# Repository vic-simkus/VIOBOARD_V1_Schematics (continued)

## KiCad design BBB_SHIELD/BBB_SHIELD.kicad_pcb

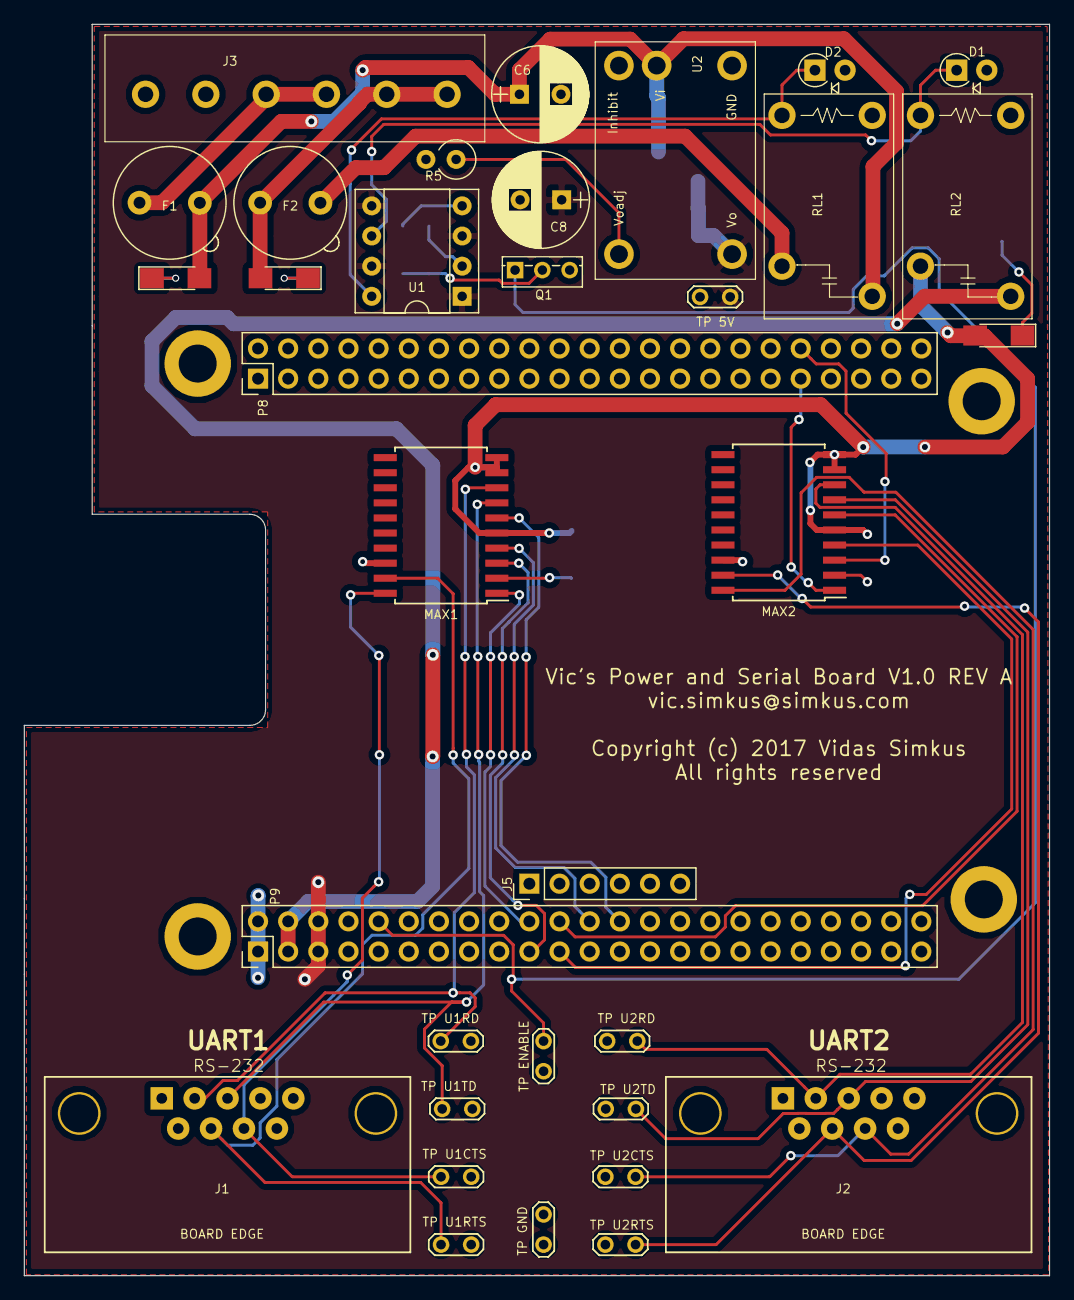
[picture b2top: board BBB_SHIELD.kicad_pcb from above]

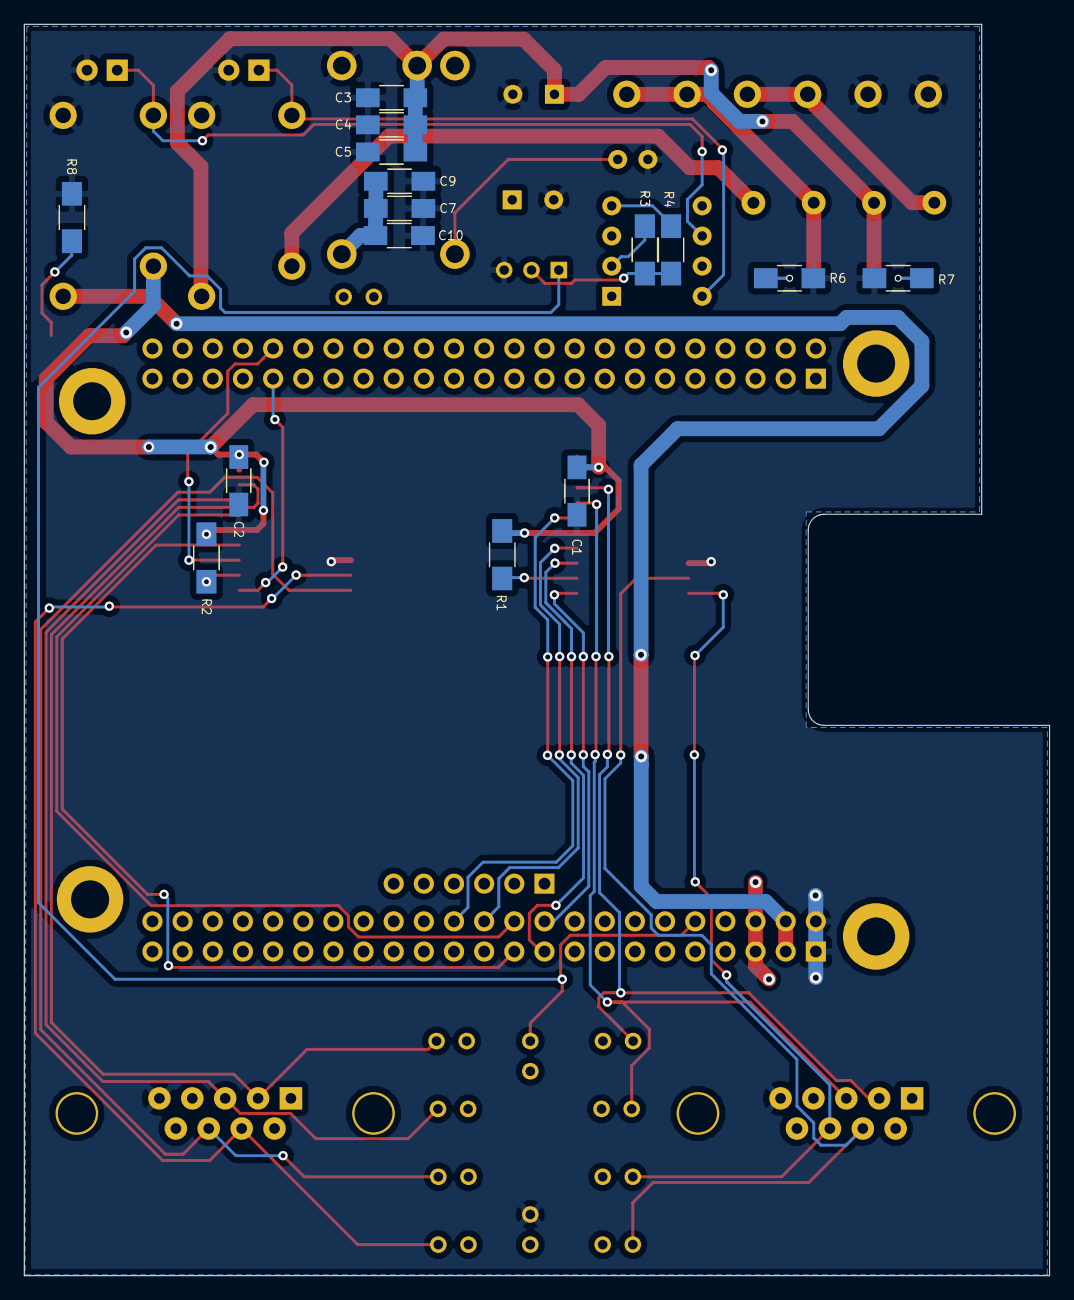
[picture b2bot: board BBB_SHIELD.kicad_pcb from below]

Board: 2 copper layers, 86.4 x 105.4 mm, 49 parts (15 on the bottom side), 36 nets.

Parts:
C1, C2: .1uF; C_1206_HandSoldering
C3, C10: 2.2uF; C_1206_HandSoldering
C4, C9: 1uF; C_1206_HandSoldering
C5, C7: 10uF; C_1206_HandSoldering
C6, C8: 180uF; CP_Radial_D8.0mm_P3.50mm
D1, D2: D; D_A-405_P2.54mm_Vertical_AnodeUp
F1, F2: Fuse; Fuseholder_Fuse_TR5_Littlefuse-No560_No460
J1: UART1; D_SUB_9_RIGHT
J2: UART2; D_SUB_9_RIGHT
J3: PWR_CONN; OSTTA064163
J4: TEST_1P; Test_Point_2Pads
J5: Screw_Terminal_1x06; Pin_Header_Straight_1x06_Pitch2.54mm
J6: TP_U1_CTS; Test_Point_2Pads
J7: TP_U1_RD; Test_Point_2Pads
J8: TP_U2_CTS; Test_Point_2Pads
J9: TP_U2_RD; Test_Point_2Pads
J10: TP_EN; Test_Point_2Pads
J11: TP_U1_TD; Test_Point_2Pads
J12: TP_U1_RTS; Test_Point_2Pads
J13: TP_U2_TD; Test_Point_2Pads
J14: TP_U2_RTS; Test_Point_2Pads
J15: TP_GND; Test_Point_2Pads
LED1: 24V_SW; LED_1206_HandSoldering
LED2: 24V_PROT; LED_1206_HandSoldering
LED3: 33V_SW; LED_1206_HandSoldering
MAX1, MAX2: MAX3233E; SOIC-20W_7.5x12.8mm_Pitch1.27mm
P8: P8; Pin_Header_Straight_2x23_Pitch2.54mm
P9: P9; Pin_Header_Straight_2x23_Pitch2.54mm
Q1: F3055L; TO-251_IPAK_Vertical
R1, R2: 10K; R_1206_HandSoldering
R3, R4, R8: 470; R_1206_HandSoldering
R5: 21K; R_Axial_DIN0309_L9.0mm_D3.2mm_P2.54mm_Vertical
R6, R7: 4.7K; R_1206_HandSoldering
RL1: 24V RELAY; OJ-SH-105LMH000-ND
RL2: 3.3V RELAY; OJ-SH-105LMH000-ND
U1: TLP222A-2-C; DIP-8_W7.62mm_Socket
U2: PTN78000WAH; PTN78000H

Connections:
/POWER_CONTROL/ENABLE: J10.1, P9.10, Q1.1
/POWER_CONTROL/VDD_24V_IN: F1.1, J3.3, J3.4
/POWER_CONTROL/VDD_24V_SW_OUT: F2.1, J3.5, J3.6, LED1.2
/SERIAL_IO/DB9_U1_CTS: J1.8, J6.1, MAX1.20
/SERIAL_IO/DB9_U1_RD(RX): J1.2, J7.1, MAX1.8
/SERIAL_IO/DB9_U1_RTS: J1.7, J12.1, MAX1.19
/SERIAL_IO/DB9_U1_TD(TX): J1.3, J11.1, MAX1.7
/SERIAL_IO/DB9_U2_CTS: J2.8, J8.1, MAX2.20
/SERIAL_IO/DB9_U2_RD(RX): J2.2, J9.1, MAX2.8
/SERIAL_IO/DB9_U2_RTS: J2.7, J14.1, MAX2.19
/SERIAL_IO/DB9_U2_TD(TX): J2.3, J13.1, MAX2.7
/U1_CTS: MAX1.1, P9.20
/U1_RTS: MAX1.3, P9.19
/U1_RX: MAX1.6, P9.26
/U1_TX: MAX1.4, P9.24
/U2_CTS: MAX2.1, P8.37
/U2_RTS: MAX2.3, P8.38
/U2_RX: MAX2.6, P9.22
/U2_TX: MAX2.4, P9.21
GND: C1.2, C2.2, C3.2, C4.2, C5.2, C6.2, C7.2, C8.2, C9.2, C10.2, D1.2, D2.2, J1.5, J2.5, J3.1, J3.2, J15.1, MAX1.18, MAX2.18, P9.1, P9.2, Q1.3, R5.2, R6.2, R7.2, R8.2, RL1.2, RL2.2, U2.1
unnamed: D1.1, RL2.1, U1.6
unnamed: D2.1, RL1.1, U1.8
unnamed: LED1.1, R6.1
unnamed: LED2.1, R7.1
unnamed: LED3.1, R8.1
unnamed: MAX1.2, R1.2
unnamed: MAX2.2, R2.2
unnamed: Q1.2, R3.2, R4.2
unnamed: R3.1, U1.2
unnamed: R4.1, U1.4
unnamed: R5.1, U2.4
VDD_5V_PROT: C7.1, C8.1, C9.1, C10.1, J4.1, P9.5, P9.6, U1.1, U1.3, U1.5, U1.7, U2.5
VDD_24V_PROT: C3.1, C4.1, C5.1, C6.1, F1.2, LED2.2, RL1.4, U2.2
VDD_24V_SW: F2.2, RL1.3
VDD_33V: P9.3, P9.4, RL2.4
VDD_33V_SW: C1.1, C2.1, LED3.2, MAX1.5, MAX1.9, MAX1.10, MAX2.5, MAX2.9, MAX2.10, R1.1, R2.1, RL2.3

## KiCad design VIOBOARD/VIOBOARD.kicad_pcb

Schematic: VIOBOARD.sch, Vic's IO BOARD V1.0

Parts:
J1: Screw_Terminal_1x04; OSTTA044163; MFGPN OSTTA044163
J2: Conn_02x02_Top_Bottom; Pin_Header_Straight_2x02_Pitch1.27mm
J8, J9: TEST_1P; Test_Point_2Pads
SW1: BOARD_RESET; SW_PUSH_6mm; MFGPN 1825910-6

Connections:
/IOCONTROLLER/IO_RESET: J2.1; also elsewhere on the board
/comm_controller/COMM_RESET: J2.3; also elsewhere on the board
/power_protection/VDD_24V: J1.1, J1.2; also elsewhere on the board
unnamed: J2.2, J2.4
RESET: SW1.2
VDD_24V_PROT: J9.1; also elsewhere on the board

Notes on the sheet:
INCOMMING POWER

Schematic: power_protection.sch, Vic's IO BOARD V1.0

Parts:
C1: 0.012uF 50V; C_1206; MFGPN 12065C123KAT2A
C2: 0.1uF 50V; C_1206; MFGPN GCM319R71H104KA37D
C3: 1uF 50V; C_1206
C4: 10uF 50V; C_1206
C5: 1nF 50V; C_1206; MFGPN GRM319R71H102KA01D
D1: 24V_TRIAC; TO-220_Vertical; MFGPN ACTT6X-800E,127
D2: D_ALT; DO-214AA; MFGPN SMBJ26A
F1: 24V_IN; Fuseholder_Fuse_TR5_Littlefuse-No560_No460; MFGPN 56000001319
LED11: Vf=2V; LED_0805; MFGPN LS R976-NR-1
R2: 23.2K 1%; R_0805; MFGPN CRCW080523K2FKEA
R3: 2.49K 1%; R_0805; MFGPN RC0805FR-072K49L
R4: 910 1%; R_0805; MFGPN CRCW0805910RFKEA
R5: 4.7K 1%; R_0805; MFGPN CRCW08054K70FKEA
R65: 100 1%; R_2512; MFGPN CRM2512-FX-1000ELF
TL1: 24V_REF; TO-92_Inline_Wide; MFGPN TL431BCLPR

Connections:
/power_protection/VDD_24V: R65.2; also elsewhere on the board
/power_protection/VDD_24V_SHUNT: D1.3, R4.2, TL1.1
unnamed: C1.1, C2.1, C3.1, C4.1, F1.1, R65.1
unnamed: C5.1, R2.2, R3.1, TL1.3
unnamed: LED11.1, R5.1
VDD_24V_PROT: D1.1, D2.1, F1.2, LED11.2, R2.1, R4.1; also elsewhere on the board

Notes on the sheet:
Vgt = 1V
Vref=2.507V
Vout = 2.520 @ Vin = 26 I = 1mA @ 26V
24V PROT
TL431
ACTT6X-800E

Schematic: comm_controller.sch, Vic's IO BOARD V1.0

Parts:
C6: 18pF 50V; C_0805; MFGPN CL21C180JBANNNC
C7: 20pF 50V; C_0805; MFGPN C0805C200K5GACTU
C8: 10uF 50V; C_1206
J3: BOARD_COMM; D_SUB_9_RIGHT; MFGPN 3-1634580-2
J12: TP SCL; Test_Point_2Pads
J13: TP SDA; Test_Point_2Pads
J14: TP_CTS; Test_Point_2Pads
J15: TP_TD; Test_Point_2Pads
J16: TP_RTS; Test_Point_2Pads
J17: TP_RD; Test_Point_2Pads
J18: TP_GND; Test_Point_2Pads
J19: CONN_01X06; Pin_Header_Angled_1x06_Pitch2.54mm; MFGPN 0022052061
LED14: Vf=2V; LED_0805; MFGPN LY R976-PS-36
PIC1: PIC24FVXXKA302; PIC_SOIC-28; MFGPN PIC24FV32KA302-I/SO
R6, R7: 4.7K 1%; R_0805; MFGPN CRCW08054K70FKEA
R8: 10K 1%; R_0805; MFGPN CRCW080510K0FKTA
R9: 470 1%; R_0805; MFGPN CRCW0805470RFKEA
Y1: 8MHz; Crystal_HC49-4H_Vertical; MFGPN 9B-8.000MEEJ-B

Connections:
/I2C_SCL: J12.1, PIC1.15, R6.2; also elsewhere on the board
/I2C_SDA: J13.1, PIC1.14, R7.2; also elsewhere on the board
/comm_controller/COMM_RESET: J19.1, PIC1.1, R8.1; also elsewhere on the board
/comm_controller/CTS: J3.8, J14.1; also elsewhere on the board
/comm_controller/RD(RX): J3.2, J17.1; also elsewhere on the board
/comm_controller/RTS: J3.7, J16.1; also elsewhere on the board
/comm_controller/TD(TX): J3.3, J15.1; also elsewhere on the board
/comm_controller/U1CTS: PIC1.17; also elsewhere on the board
/comm_controller/U1RTS: PIC1.18; also elsewhere on the board
/comm_controller/U1RX: PIC1.6; also elsewhere on the board
/comm_controller/U1TX: PIC1.16; also elsewhere on the board
unnamed: C6.1, PIC1.9, Y1.1
unnamed: C7.1, PIC1.10, Y1.2
unnamed: C8.2, PIC1.20
unnamed: J19.4, PIC1.4
unnamed: J19.5, PIC1.5
unnamed: LED14.1, R9.2
unnamed: LED14.2, PIC1.25
VDD_5V_PROT: J19.2, PIC1.13, PIC1.28, R6.1, R7.1, R8.2; also elsewhere on the board

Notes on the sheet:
RB0 - ICSP - PGED
RB1 - ICSP - PGEC
RB2 - U1RX - RS1_OUT
RB5 - ASDA
RB6 - ASCL
RB7 - U1TX - TTL1_IN
RB8 - U1CTS - RS2_OUT
RB9 - U1RTS - TTL2_IN
RB14 - GPIO
SDA
SCL
BOM - 2017-06-09
COMMHTBT

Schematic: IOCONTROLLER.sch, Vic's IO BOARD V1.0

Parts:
C18: 20pF 50V; C_0805; MFGPN C0805C200K5GACTU
C19: 18pF 50V; C_0805; MFGPN CL21C180JBANNNC
J20: CONN_01X06; Pin_Header_Angled_1x06_Pitch2.54mm; MFGPN 0022052061
R10: 10K 1%; R_0805; MFGPN CRCW080510K0FKTA
Y2: 10MHz; Crystal_HC49-4H_Vertical; MFGPN 9B-10.000MEEJ-B
dsPIC1: dsPIC30F4013; TQFP-44_10x10mm_Pitch0.8mm; MFGPN DSPIC30F4013-30I/PT

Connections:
/I2C_SCL: dsPIC1.44; also elsewhere on the board
/I2C_SDA: dsPIC1.1; also elsewhere on the board
/IOCONTROLLER/AI_ENABLE/RC13: dsPIC1.32; also elsewhere on the board
/IOCONTROLLER/AI_FAULT/R0: dsPIC1.9; also elsewhere on the board
/IOCONTROLLER/AI_PROT/PP_AI_FAULT_LED: dsPIC1.36; also elsewhere on the board
/IOCONTROLLER/AN3/RB3/420_4: dsPIC1.22; also elsewhere on the board
/IOCONTROLLER/AN4/RB4/420_3: dsPIC1.23; also elsewhere on the board
/IOCONTROLLER/AN5/RB5/420_2: dsPIC1.24; also elsewhere on the board
/IOCONTROLLER/AN8/RB8/420_1: dsPIC1.27; also elsewhere on the board
/IOCONTROLLER/AUX_LED: dsPIC1.35; also elsewhere on the board
/IOCONTROLLER/BUS_IN_LED: dsPIC1.37; also elsewhere on the board
/IOCONTROLLER/BUS_OUT_LED: dsPIC1.41; also elsewhere on the board
/IOCONTROLLER/DIGITAL_OUT/PP_DO_FAULT_LED: dsPIC1.38; also elsewhere on the board
/IOCONTROLLER/DO1/RF1: dsPIC1.4; also elsewhere on the board
/IOCONTROLLER/DO2/RF0: dsPIC1.5; also elsewhere on the board
/IOCONTROLLER/DO3/RF6: dsPIC1.43; also elsewhere on the board
/IOCONTROLLER/DO4/RF4: dsPIC1.3; also elsewhere on the board
/IOCONTROLLER/DO_ENABLE/RF5: dsPIC1.2; also elsewhere on the board
/IOCONTROLLER/DO_FAULT/RD1: dsPIC1.8; also elsewhere on the board
/IOCONTROLLER/DSPIC_PGC: J20.5, dsPIC1.25
/IOCONTROLLER/DSPIC_PGD: J20.4, dsPIC1.26
/IOCONTROLLER/HTBT_LED: dsPIC1.42; also elsewhere on the board
/IOCONTROLLER/IO_RESET: J20.1, R10.1, dsPIC1.18; also elsewhere on the board
/IOCONTROLLER/RB1/AN1/ICD3: dsPIC1.20; also elsewhere on the board
/IOCONTROLLER/RB2/AN2/ICD4: dsPIC1.21; also elsewhere on the board
/IOCONTROLLER/RB9/AN9/ICD1: dsPIC1.15; also elsewhere on the board
/IOCONTROLLER/RB10/AN10/ICD2: dsPIC1.14; also elsewhere on the board
/IOCONTROLLER/VREF+/VREF+: dsPIC1.19; also elsewhere on the board
unnamed: C18.2, Y2.1, dsPIC1.31
unnamed: C19.2, Y2.2, dsPIC1.30
VDD_5V_PROT: J20.2, R10.2, dsPIC1.7, dsPIC1.17, dsPIC1.28, dsPIC1.40; also elsewhere on the board

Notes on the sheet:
BOM - 2017-06-09

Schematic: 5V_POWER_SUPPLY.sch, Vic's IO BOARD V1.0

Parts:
C44: 2.2uF 50V; C_1206; MFGPN GCM31CR71H225KA55L
C45: 1uF 50V; C_1206; MFGPN GRM31CR71H105KA61L
C46, C48: 10uF 50V; C_1206; MFGPN CL31B106KBHNNNE
C47, C49: 180uF; CP_Radial_D8.0mm_P3.50mm; MFGPN EEU-FC1H181L
C50: 1uF 50V; C_0805; MFGPN CL21B105KBFNNNF
C51: 2.2uF 50V; C_0805; MFGPN C2012X7R1H225K125AC
J11: TEST_1P; Test_Point_2Pads
R45: 21K 1%; R_0805; MFGPN CRCW080521K0FKEA
R66, R67, R68, R69: 0 1%; R_0805; MFGPN CRCW08050000Z0EBC
U9: PTN78000WAH; PTN78000H; MFGPN PTN78000WAH

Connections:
unnamed: C44.1, R66.2
unnamed: C45.1, R67.2
unnamed: C46.1, R68.2
unnamed: C47.1, R69.2
unnamed: R45.1, U9.4
VDD_5V_PROT: C48.1, C49.1, C50.1, C51.1, J11.1, U9.5; also elsewhere on the board
VDD_24V_PROT: R66.1, R67.1, R68.1, R69.1, U9.2; also elsewhere on the board

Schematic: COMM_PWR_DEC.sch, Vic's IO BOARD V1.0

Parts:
C10: 0.01uF 50V; C_0805; MFGPN CL21B103KBANNNC
C11: 0.1uF 50V; C_0805; MFGPN CL21B104KBCNNNC
C12: 1uF 50V; C_0805; MFGPN CL21B105KBFNNNF
C13: 10uF 50V; C_1206

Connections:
VDD_5V_PROT: C10.1, C11.1, C12.1, C13.1; also elsewhere on the board

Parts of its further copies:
C14: 0.01uF 50V; C_0805; MFGPN CL21B103KBANNNC
C15: 0.1uF 50V; C_0805; MFGPN CL21B104KBCNNNC
C16: 1uF 50V; C_0805; MFGPN CL21B105KBFNNNF
C17: 10uF 50V; C_1206

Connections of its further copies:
VDD_5V_PROT: C14.1, C15.1, C16.1, C17.1; also elsewhere on the board

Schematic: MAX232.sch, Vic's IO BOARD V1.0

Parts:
C60, C61, C62, C63, C64: 1uF 50V; C_0805; MFGPN CL21B105KBFNNNF
U1: MAX232I; SOIC-16_3.9x9.9mm_Pitch1.27mm; MFGPN MAX232ID

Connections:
/comm_controller/CTS: U1.8 (R2IN); also elsewhere on the board
/comm_controller/RD(RX): U1.13 (R1IN); also elsewhere on the board
/comm_controller/RTS: U1.7 (T2OUT); also elsewhere on the board
/comm_controller/TD(TX): U1.14 (T1OUT); also elsewhere on the board
/comm_controller/U1CTS: U1.9 (R2OUT); also elsewhere on the board
/comm_controller/U1RTS: U1.10 (T2IN); also elsewhere on the board
/comm_controller/U1RX: U1.12 (R1OUT); also elsewhere on the board
/comm_controller/U1TX: U1.11 (T1IN); also elsewhere on the board
unnamed: C60.1, U1.1 (C1+)
unnamed: C60.2, U1.3 (C1-)
unnamed: C61.1, U1.4 (C2+)
unnamed: C61.2, U1.5 (C2-)
unnamed: C62.1, U1.2 (VS+)
unnamed: C63.1, U1.6 (VS-)
VDD_5V_PROT: C64.1, U1.16 (VCC); also elsewhere on the board

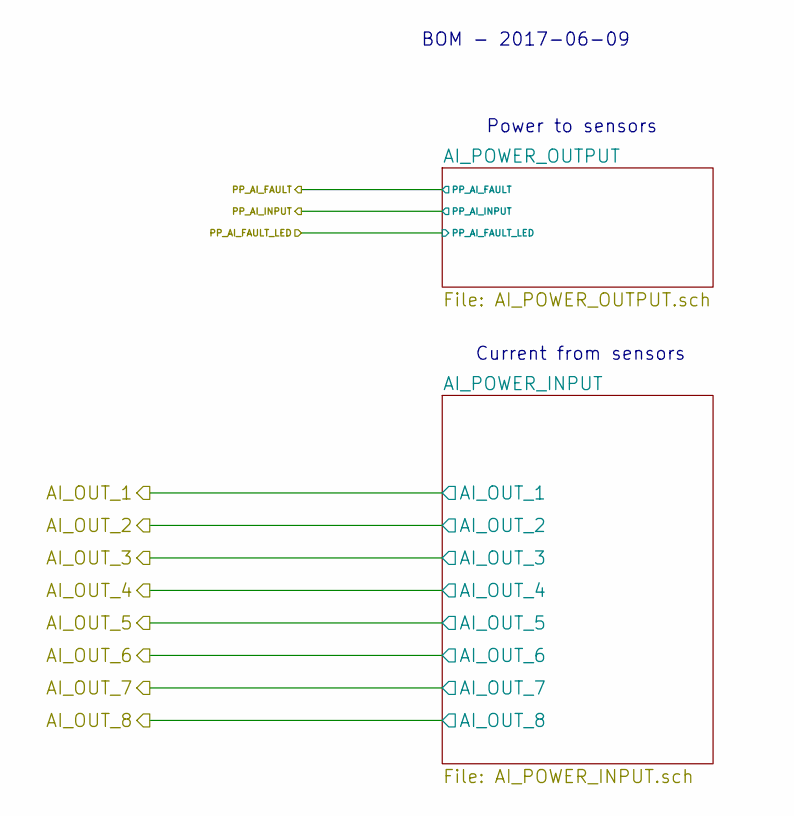
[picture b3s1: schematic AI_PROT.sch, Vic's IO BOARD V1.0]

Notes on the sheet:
Power to sensors
Current from sensors
BOM - 2017-06-09

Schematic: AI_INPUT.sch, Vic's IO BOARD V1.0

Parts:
C21: 0.01uF 50V; C_0805; MFGPN CL21B103KBANNNC
C22: 0.1uF 50V; C_0805; MFGPN CL21B104KBCNNNC
C23, C52, C53, C54, C55, C56, C57, C58, C59: 1uF 50V; C_0805; MFGPN CL21B105KBFNNNF
C24: 10uF 50V; C_1206
R20, R22, R24, R28: 910 1%; R_0805; MFGPN RC2012F822CS
R21, R23, R26, R30: 8.2K 1%; R_0805; MFGPN CRCW0805910RFKEA
R25, R27, R29, R31: 250 0.1%; R_Axial_DIN0309_L9.0mm_D3.2mm_P2.54mm_Vertical; MFGPN CMF55250R00BHEK
R32, R33, R34, R35: 1K 0.1%; R_0805; MFGPN ERJ-PB6B1001V
R78, R79, R80, R81, R82, R83, R84, R85: 1K 1%; R_0805; MFGPN CRCW08051K00FKEA
U5: MCP6004_C; SOIC-14_3.9x8.7mm_Pitch1.27mm; MFGPN MCP6004T-I/SL

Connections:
/IOCONTROLLER/AI_INPUT/AI_IN_420_1: R31.2, R80.1; also elsewhere on the board
/IOCONTROLLER/AI_INPUT/AI_IN_420_2: R29.2, R82.1; also elsewhere on the board
/IOCONTROLLER/AI_INPUT/AI_IN_420_3: R27.2, R84.1; also elsewhere on the board
/IOCONTROLLER/AI_INPUT/AI_IN_420_4: R25.2, R85.1; also elsewhere on the board
/IOCONTROLLER/AI_INPUT/AI_IN_ICD_1: R35.2, U5.3; also elsewhere on the board
/IOCONTROLLER/AI_INPUT/AI_IN_ICD_2: R34.2, U5.5; also elsewhere on the board
/IOCONTROLLER/AI_INPUT/AI_IN_ICD_3: R33.2, U5.10; also elsewhere on the board
/IOCONTROLLER/AI_INPUT/AI_IN_ICD_4: R32.2, U5.12; also elsewhere on the board
/IOCONTROLLER/AI_INPUT/Vina-: R28.2, R30.2, U5.2
/IOCONTROLLER/AI_INPUT/Vinb-: R24.2, R26.2, U5.6
/IOCONTROLLER/AI_INPUT/Vinc-: R22.2, R23.2, U5.9
/IOCONTROLLER/AI_INPUT/Vind-: R20.2, R21.2, U5.13
/IOCONTROLLER/AI_INPUT/Vouta: R30.1, R83.1, U5.1
/IOCONTROLLER/AI_INPUT/Voutb: R26.1, R81.1, U5.7
/IOCONTROLLER/AI_INPUT/Voutc: R23.1, R79.1, U5.8
/IOCONTROLLER/AI_INPUT/Voutd: R21.1, R78.1, U5.14
/IOCONTROLLER/AN3/RB3/420_4: C58.2, R85.2; also elsewhere on the board
/IOCONTROLLER/AN4/RB4/420_3: C56.2, R84.2; also elsewhere on the board
/IOCONTROLLER/AN5/RB5/420_2: C54.2, R82.2; also elsewhere on the board
/IOCONTROLLER/AN8/RB8/420_1: C52.2, R80.2; also elsewhere on the board
/IOCONTROLLER/RB1/AN1/ICD3: C55.1, R79.2; also elsewhere on the board
/IOCONTROLLER/RB2/AN2/ICD4: C53.1, R78.2; also elsewhere on the board
/IOCONTROLLER/RB9/AN9/ICD1: C59.1, R83.2; also elsewhere on the board
/IOCONTROLLER/RB10/AN10/ICD2: C57.1, R81.2; also elsewhere on the board
VDD_5V_PROT: C21.2, C22.1, C23.1, C24.1, U5.4; also elsewhere on the board

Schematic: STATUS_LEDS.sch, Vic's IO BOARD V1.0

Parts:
LED2: Vf=2V; LED_0805; MFGPN LY R976-PS-36
LED3, LED4, LED5: Vf=2V; LED_0805; MFGPN LS R976-NR-1
R1, R46, R47, R48: 470 1%; R_0805; MFGPN CRCW0805470RFKEA

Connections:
/IOCONTROLLER/AUX_LED: LED5.2; also elsewhere on the board
/IOCONTROLLER/BUS_IN_LED: LED3.2; also elsewhere on the board
/IOCONTROLLER/BUS_OUT_LED: LED4.2; also elsewhere on the board
/IOCONTROLLER/HTBT_LED: LED2.2; also elsewhere on the board
unnamed: LED2.1, R1.2
unnamed: LED3.1, R46.2
unnamed: LED4.1, R47.2
unnamed: LED5.1, R48.2

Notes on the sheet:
BOM - 2017-06-09
HTBT LED is yellow

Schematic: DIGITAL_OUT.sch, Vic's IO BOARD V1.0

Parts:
D20, D21, D22, D23: D_ALT; D_SOD-323_CUSTOM; MFGPN CUS08F30,H3F
J7: Screw_Terminal_1x04; OSTTA044163; MFGPN OSTTA044163
LED6, LED7, LED8, LED9: Vf=2V; LED_0805; MFGPN LS R976-NR-1
R49, R50, R51, R52: 470 1%; R_0805; MFGPN CRCW0805470RFKEA
R61, R62, R63, R64: 100 1%; R_0805; MFGPN ERJ-P06F1000V
R86, R87, R88, R89: 4.7K 1%; R_0805; MFGPN CRCW08054K70FKEA
TLPA1: TLP222A-2-C; DIP-8_W7.62mm_Socket; MFGPN TLP222A-2(F)
TLPB1: TLP222A-2-C; DIP-8_W7.62mm_Socket; MFGPN TLP222A-2(F)

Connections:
/IOCONTROLLER/DIGITAL_OUT/DO_POWER_OUT: TLPA1.5, TLPA1.7, TLPB1.5, TLPB1.7; also elsewhere on the board
/IOCONTROLLER/DO1/RF1: TLPA1.3; also elsewhere on the board
/IOCONTROLLER/DO2/RF0: TLPA1.1; also elsewhere on the board
/IOCONTROLLER/DO3/RF6: TLPB1.1; also elsewhere on the board
/IOCONTROLLER/DO4/RF4: TLPB1.3; also elsewhere on the board
unnamed: D20.1, R61.2
unnamed: D20.2, LED6.2, TLPA1.6
unnamed: D21.1, R62.2
unnamed: D21.2, LED7.2, TLPA1.8
unnamed: D22.1, R63.2
unnamed: D22.2, LED8.2, TLPB1.6
unnamed: D23.1, R64.2
unnamed: D23.2, LED9.2, TLPB1.8
unnamed: J7.1, R61.1
unnamed: J7.2, R62.1
unnamed: J7.3, R63.1
unnamed: J7.4, R64.1
unnamed: LED6.1, R86.1
unnamed: LED7.1, R87.1
unnamed: LED8.1, R88.1
unnamed: LED9.1, R89.1
unnamed: R49.1, TLPB1.2
unnamed: R50.1, TLPB1.4
unnamed: R51.1, TLPA1.2
unnamed: R52.1, TLPA1.4

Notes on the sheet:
DOUT
DOUT2
DOUT3
DOUT4

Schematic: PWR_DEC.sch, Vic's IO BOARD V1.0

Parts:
C26: 0.01uF 50V; C_0805; MFGPN CL21B103KBANNNC
C27: 0.1uF 50V; C_0805; MFGPN CL21B104KBCNNNC
C28: 1uF 50V; C_0805; MFGPN CL21B105KBFNNNF
C29: 10uF 50V; C_1206

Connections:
VDD_5V_PROT: C26.1, C27.1, C28.1, C29.1; also elsewhere on the board

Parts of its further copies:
C30, C34, C38: 0.01uF 50V; C_0805; MFGPN CL21B103KBANNNC
C31, C35, C39: 0.1uF 50V; C_0805; MFGPN CL21B104KBCNNNC
C32, C36, C40: 1uF 50V; C_0805; MFGPN CL21B105KBFNNNF
C33, C37, C41: 10uF 50V; C_1206

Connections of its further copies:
VDD_5V_PROT: C30.1, C31.1, C32.1, C33.1, C34.1, C35.1, C36.1, C37.1, C38.1, C39.1, C40.1, C41.1; also elsewhere on the board

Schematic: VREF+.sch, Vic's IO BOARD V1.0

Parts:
C42: 0.1uF 50V; C_1206
C43: 0.1uF 50V; C_0805; MFGPN CL21B104KBCNNNC
J10: TEST_1P; Test_Point_2Pads
U7: REF02CSZ; SOIC-8_3.9x4.9mm_Pitch1.27mm; MFGPN REF02CSZ

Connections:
/IOCONTROLLER/VREF+/VREF+: C43.1, J10.1, U7.6; also elsewhere on the board
VDD_24V_PROT: C42.1, U7.2; also elsewhere on the board

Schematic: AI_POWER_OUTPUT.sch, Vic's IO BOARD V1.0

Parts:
D24, D25, D26, D27, D28, D29, D30, D31: D_ALT; D_SOD-323_CUSTOM; MFGPN CUS08F30,H3F
J5: 24V OUTPUT; OSTTA084163; MFGPN OSTTA084163
R70, R71, R72, R73, R74, R75, R76, R77: 100 1%; R_0805; MFGPN ERJ-P06F1000V

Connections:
/IOCONTROLLER/AI_PROT/AI_POWER_OUTPUT/SENSOR_OUT: D24.2, D25.2, D26.2, D27.2, D28.2, D29.2, D30.2, D31.2; also elsewhere on the board
unnamed: D24.1, R70.2
unnamed: D25.1, R71.2
unnamed: D26.1, R72.2
unnamed: D27.1, R73.2
unnamed: D28.1, R74.2
unnamed: D29.1, R75.2
unnamed: D30.1, R76.2
unnamed: D31.1, R77.2
unnamed: J5.1, R77.1
unnamed: J5.2, R76.1
unnamed: J5.3, R75.1
unnamed: J5.4, R74.1
unnamed: J5.5, R73.1
unnamed: J5.6, R72.1
unnamed: J5.7, R71.1
unnamed: J5.8, R70.1

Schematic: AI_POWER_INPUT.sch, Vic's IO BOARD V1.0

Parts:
D4, D13, D14, D15, D16, D17, D18, D19: BAS70-04; SOT-23; MFGPN BAS70-04-E3-08
J6: SENSOR INPUT; OSTTA084163; MFGPN OSTTA084163
R53, R54, R55, R56, R57, R58, R59, R60: 100 1%; R_0805; MFGPN ERJ-P06F1000V

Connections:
/IOCONTROLLER/AI_INPUT/AI_IN_420_1: J6.1, R60.1; also elsewhere on the board
/IOCONTROLLER/AI_INPUT/AI_IN_420_2: J6.2, R59.1; also elsewhere on the board
/IOCONTROLLER/AI_INPUT/AI_IN_420_3: J6.3, R58.1; also elsewhere on the board
/IOCONTROLLER/AI_INPUT/AI_IN_420_4: J6.4, R57.1; also elsewhere on the board
/IOCONTROLLER/AI_INPUT/AI_IN_ICD_1: J6.5, R56.1; also elsewhere on the board
/IOCONTROLLER/AI_INPUT/AI_IN_ICD_2: J6.6, R55.1; also elsewhere on the board
/IOCONTROLLER/AI_INPUT/AI_IN_ICD_3: J6.7, R54.1; also elsewhere on the board
/IOCONTROLLER/AI_INPUT/AI_IN_ICD_4: J6.8, R53.1; also elsewhere on the board
unnamed: D4.3, R53.2
unnamed: D13.3, R54.2
unnamed: D14.3, R55.2
unnamed: D15.3, R56.2
unnamed: D16.3, R57.2
unnamed: D17.3, R58.2
unnamed: D18.3, R59.2
unnamed: D19.3, R60.2
VDD_5V_PROT: D4.2, D13.2, D14.2, D15.2, D16.2, D17.2, D18.2, D19.2; also elsewhere on the board

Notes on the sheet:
BOM - 2017-06-09

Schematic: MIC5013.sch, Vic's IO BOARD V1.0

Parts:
C20: 10uF 50V; C_1206
LED1, LED12: Vf=2V; LED_0805; MFGPN LS R976-NR-1
Q1: RFD3055LE; TO-251_IPAK_Vertical; MFGPN RFD3055LE
R11, R12: 10K 1%; R_0805; MFGPN CRCW080510K0FKTA
R13: 8.2K 1%; R_0805; MFGPN RC2012F822CS
R14: 2.2K 1%; R_0805; MFGPN RMCF0805FT2K20
R15: 470 1%; R_0805; MFGPN CRCW0805470RFKEA
R16: 24K 1%; R_0805; MFGPN RMCF0805FT24K0
R17: 100 1%; R_0805; MFGPN ERJ-P06F1000V
R18: 3 1%; R_0805; MFGPN ERJ-6DQF3R0V
R19: 4.7K 1%; R_0805; MFGPN CRCW08054K70FKEA
U2: MIC5013; SOIC-8_3.9x4.9mm_Pitch1.27mm; MFGPN MIC5013YM

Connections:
/IOCONTROLLER/AI_ENABLE/RC13: R11.2, U2.1; also elsewhere on the board
/IOCONTROLLER/AI_FAULT/R0: R13.1, R14.2; also elsewhere on the board
/IOCONTROLLER/AI_PROT/AI_POWER_OUTPUT/ANALOG_OUTPUT_POWER/FAULT: R13.2, U2.8
/IOCONTROLLER/AI_PROT/AI_POWER_OUTPUT/ANALOG_OUTPUT_POWER/GATE: Q1.1, U2.6
/IOCONTROLLER/AI_PROT/AI_POWER_OUTPUT/ANALOG_OUTPUT_POWER/SENSE: R16.1, R17.2, U2.3
/IOCONTROLLER/AI_PROT/AI_POWER_OUTPUT/ANALOG_OUTPUT_POWER/THRESH: R12.1, U2.2
/IOCONTROLLER/AI_PROT/AI_POWER_OUTPUT/SENSOR_OUT: LED12.2, R18.2, U2.4; also elsewhere on the board
/IOCONTROLLER/AI_PROT/PP_AI_FAULT_LED: LED1.2; also elsewhere on the board
unnamed: LED1.1, R15.1
unnamed: LED12.1, R19.1
unnamed: Q1.3, R17.1, R18.1
VDD_24V_PROT: C20.1, Q1.2, U2.7; also elsewhere on the board

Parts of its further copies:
C25: 10uF 50V; C_1206
LED10, LED13: Vf=2V; LED_0805; MFGPN LS R976-NR-1
Q2: RFD3055LE; TO-251_IPAK_Vertical; MFGPN RFD3055LE
R36, R37: 10K 1%; R_0805; MFGPN CRCW080510K0FKTA
R38: 8.2K 1%; R_0805; MFGPN RC2012F822CS
R39: 2.2K 1%; R_0805; MFGPN RMCF0805FT2K20
R40: 470 1%; R_0805; MFGPN CRCW0805470RFKEA
R41: 24K 1%; R_0805; MFGPN RMCF0805FT24K0
R42: 100 1%; R_0805; MFGPN ERJ-P06F1000V
R43: 3 1%; R_0805; MFGPN ERJ-6DQF3R0V
R44: 4.7K 1%; R_0805; MFGPN CRCW08054K70FKEA
U6: MIC5013; SOIC-8_3.9x4.9mm_Pitch1.27mm; MFGPN MIC5013YM

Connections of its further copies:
/IOCONTROLLER/DIGITAL_OUT/DIGITAL_OUT_POWER/FAULT: R38.2, U6.8
/IOCONTROLLER/DIGITAL_OUT/DIGITAL_OUT_POWER/GATE: Q2.1, U6.6
/IOCONTROLLER/DIGITAL_OUT/DIGITAL_OUT_POWER/SENSE: R41.1, R42.2, U6.3
/IOCONTROLLER/DIGITAL_OUT/DIGITAL_OUT_POWER/THRESH: R37.1, U6.2
/IOCONTROLLER/DIGITAL_OUT/DO_POWER_OUT: LED13.2, R43.2, U6.4; also elsewhere on the board
/IOCONTROLLER/DIGITAL_OUT/PP_DO_FAULT_LED: LED10.2; also elsewhere on the board
/IOCONTROLLER/DO_ENABLE/RF5: R36.2, U6.1; also elsewhere on the board
/IOCONTROLLER/DO_FAULT/RD1: R38.1, R39.2; also elsewhere on the board
unnamed: LED10.1, R40.1
unnamed: LED13.1, R44.1
unnamed: Q2.3, R42.1, R43.1
VDD_24V_PROT: C25.1, Q2.2, U6.7; also elsewhere on the board

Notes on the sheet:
FAULT LED

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
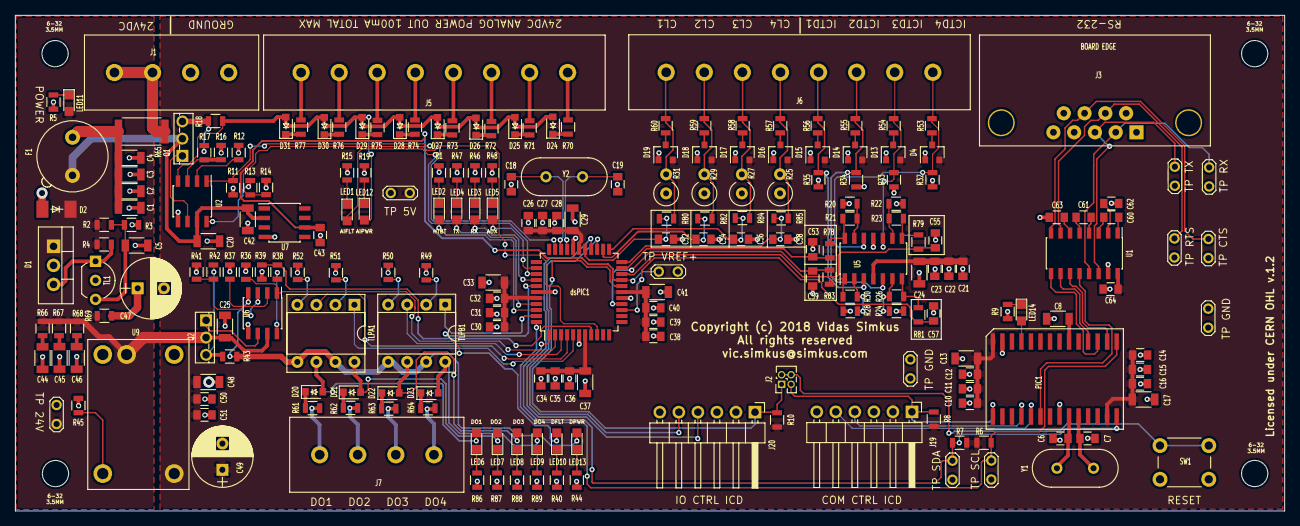
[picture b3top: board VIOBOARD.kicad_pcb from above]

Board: 2 copper layers, 169.3 x 66.1 mm, 224 parts (0 on the bottom side), 146 nets.

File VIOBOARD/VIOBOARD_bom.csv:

Component|Description|Part|References|Value|Footprint|Quantity Per PCB|MFGPN|DKPN|MFG
1|Unpolarized capacitor|C_Small|C1|0.012uF 50V|C_1206|1|12065C123KAT2A|478-1543-1-ND|
2|Unpolarized capacitor|C_Small|C10 C14 C21 C26 C30 C34 C38|0.01uF 50V|C_0805|7|CL21B103KBANNNC|1276-1015-1-ND|
3|Unpolarized capacitor|C_Small|C11 C15 C22 C27 C31 C35 C39 C43|0.1uF 50V|C_0805|8|CL21B104KBCNNNC|1276-1003-1-ND|
4|Unpolarized capacitor|C_Small|C2 C42|0.1uF 50V|C_1206|2|GCM319R71H104KA37D|490-11166-1-ND|
5|Unpolarized capacitor|C_Small|C4 C8 C13 C17 C20 C24 C25 C29 C33 C37 C41 C46 C48|10uF 50V|C_1206|13|CL31B106KBHNNNE|1276-6767-1-ND|
6|Polarised capacitor|CP1_Small|C47 C49|180uF|CP_Radial_D8.0mm_P3.50mm|2|EEU-FC1H181L|P10324-ND|Panasonic
7|Unpolarized capacitor|C_Small|C6 C19|18pF 50V|C_0805|2|CL21C180JBANNNC|1276-1107-1-ND|
8|Unpolarized capacitor|C_Small|C5|1nF 50V|C_1206|1|GRM319R71H102KA01D|490-11610-1-ND|
9|Unpolarized capacitor|C_Small|C12 C16 C23 C28 C32 C36 C40 C50 C52 C53 C54 C55 C56 C57 C58 C59 C60 C61 C62 C63 C64|1uF 50V|C_0805|21|CL21B105KBFNNNF|1276-6470-1-ND|
10|Unpolarized capacitor|C_Small|C3 C45|1uF 50V|C_1206|2|GRM31CR71H105KA61L|490-3908-1-ND|
11|Unpolarized capacitor|C_Small|C44|2.2uF 50V|C_1206|1|GCM31CR71H225KA55L|490-4796-1-ND|
12|Unpolarized capacitor|C_Small|C51|2.2uF 50V|C_0805|1|C2012X7R1H225K125AC|445-5968-1-ND|
13|Unpolarized capacitor|C_Small|C7 C18|20pF 50V|C_0805|2|C0805C200K5GACTU|399-14568-2-ND|
14|triode for alternating current (TRIAC)|Q_TRIAC_AAG|D1|24V_TRIAC|TO-220_Vertical|1|ACTT6X-800E,127|1740-1006-ND|
15|Dual schottky diode|D_Schottky_x2_Serial_AKC|D4 D13 D14 D15 D16 D17 D18 D19|BAS70-04|SOT-23|8|BAS70-04-E3-08|BAS70-04-E3-08CT-ND|
16|Diode, alternativ symbol|D_ALT|D2|D_ALT|DO-214AA|1|SMBJ26A|SMBJ26ALFCT-ND|
17|Diode, alternativ symbol|D_ALT|D20 D21 D22 D23 D24 D25 D26 D27 D28 D29 D30 D31|D_ALT|D_SOD-323_CUSTOM|12|CUS08F30,H3F|CUS08F30H3FCT-ND|
18|Fuse, small symbol|Fuse_Small|F1|24V_IN|Fuseholder_Fuse_TR5_Littlefuse-No560_No460|1|56000001319|WK0001-ND|
19||Screw_Terminal_1x08|J5|24V OUTPUT|OSTTA084163|1|OSTTA084163|ED2586-ND|
20||DB9_MALE|J3|BOARD_COMM|D_SUB_9_RIGHT|1|3-1634580-2|A118453-ND|
21||CONN_01X06|J19 J20|CONN_01X06|Pin_Header_Angled_1x06_Pitch2.54mm|2|0022052061|WM4104-ND|
22||Screw_Terminal_1x08|J6|SENSOR INPUT|OSTTA084163|1|OSTTA084163|ED2586-ND|
23||Screw_Terminal_1x04|J1 J7|Screw_Terminal_1x04|OSTTA044163|2|OSTTA044163|ED2582-ND|
24|LED generic, alternativ symbol|LED_ALT|LED1 LED3 LED4 LED5 LED6 LED7 LED8 LED9 LED10 LED11 LED12 LED13|Vf=2V|LED_0805|12|LS R976-NR-1|475-1278-2-ND|
25|LED generic, alternativ symbol|LED_ALT|LED2 LED14|Vf=2V|LED_0805|2|LY R976-PS-36|475-2560-2-ND|
26|Microcontroller, PIC24FV|PIC24FVXXKA302|PIC1|PIC24FVXXKA302|PIC_SOIC-28|1|PIC24FV32KA302-I/SO|PIC24FV32KA302-I/SO-ND|
27|Transistor N-MOSFET with substrate diode (general)|Q_NMOS_GDS|Q1 Q2|RFD3055LE|TO-251_IPAK_Vertical|2|RFD3055LE|RFD3055LE-ND|
28|Resistor|R|R66 R67 R68 R69|0 1%|R_0805|4|CRCW08050000Z0EBC|541-4126-1-ND|
29|Resistor|R_C|R17 R42 R53 R54 R55 R56 R57 R58 R59 R60 R61 R62 R63 R64 R70 R71 R72 R73 R74 R75 R76 R77|100 1%|R_0805|22|ERJ-P06F1000V|P16057CT-ND|
30|Resistor|R|R65|100 1%|R_2512|1|CRM2512-FX-1000ELF|CRM2512-FX-1000ELFCT-ND|
31|Resistor|R_C|R8 R10 R11 R12 R36 R37|10K 1%|R_0805|6|CRCW080510K0FKTA|541-3016-1-ND|
32|Resistor|R_C|R32 R33 R34 R35|1K 0.1%|R_0805|4|ERJ-PB6B1001V|P20594CT-ND|
33|Resistor, small symbol|R_Small|R78 R79 R80 R81 R82 R83 R84 R85|1K 1%|R_0805|8|CRCW08051K00FKEA|541-1.00KCCT-ND|
34|Resistor|R_C|R14 R39|2.2K 1%|R_0805|2|RMCF0805FT2K20|RMCF0805FT2K20CT-ND|
35|Resistor|R_C|R3|2.49K 1%|R_0805|1|RC0805FR-072K49L|311-2.49KCRCT-ND|
36|Resistor|R_C|R45|21K 1%|R_0805|1|CRCW080521K0FKEA|541-21.0KCCT-ND|
37|Resistor|R_C|R2|23.2K 1%|R_0805|1|CRCW080523K2FKEA|541-23.2KCCT-ND|
38|Resistor|R_C|R16 R41|24K 1%|R_0805|2|RMCF0805FT24K0|RMCF0805FT24K0CT-ND|
39|Resistor|R_C|R25 R27 R29 R31|250 0.1%|R_Axial_DIN0309_L9.0mm_D3.2mm_P2.54mm_Vertical|4|CMF55250R00BHEK|CMF250HD-ND|
40|Resistor|R_C|R18 R43|3 1%|R_0805|2|ERJ-6DQF3R0V|P19279CT-ND|
41|Resistor|R_C|R5 R6 R7 R19 R44 R86 R87 R88 R89|4.7K 1%|R_0805|9|CRCW08054K70FKEA|541-4.70KCCT-ND|
42|Resistor|R_C|R1 R9 R15 R40 R46 R47 R48 R49 R50 R51 R52|470 1%|R_0805|11|CRCW0805470RFKEA|541-470CCT-ND|
43|Resistor|R_C|R13 R38|8.2K 1%|R_0805|2|RC2012F822CS|1276-5326-2-ND|
44|Resistor|R_C|R21 R23 R26 R30|8.2K 1%|R_0805|4|CRCW0805910RFKEA|541-910CCT-ND|
45|Resistor|R_C|R20 R22 R24 R28|910 1%|R_0805|4|RC2012F822CS|1276-5326-1-ND|
46|Resistor|R_C|R4|910 1%|R_0805|1|CRCW0805910RFKEA|541-910CCT-ND|
47|Single Pole Single Throw (SPST) switch|SW_SPST|SW1|BOARD_RESET|SW_PUSH_6mm|1|1825910-6|450-1650-ND|
48|Voltage reference, shunt, adjustable|TL431|TL1|24V_REF|TO-92_Inline_Wide|1|TL431BCLPR|296-17374-1-ND|
49|Relay, optical, dual|TLP222A-2-C|TLPA1 TLPB1|TLP222A-2-C|DIP-8_W7.62mm_Socket|2|TLP222A-2(F)|TLP222A-2F-ND|
50|Dual RS232 driver/receiver, 5V supply, 120kb/s, 0C-70C|MAX232I|U1|MAX232I|SOIC-16_3.9x9.9mm_Pitch1.27mm|1|MAX232ID|296-6938-5-ND|TI
51|Opamp, quad|MCP6004_C|U5|MCP6004_C|SOIC-14_3.9x8.7mm_Pitch1.27mm|1|MCP6004T-I/SL|MCP6004T-I/SLCT-ND|
52|Driver, hi/low side, with overcurrent monitoring |MIC5013|U2 U6|MIC5013|SOIC-8_3.9x4.9mm_Pitch1.27mm|2|MIC5013YM|576-1231-ND|
53|Voltage regulator, switching|PTN78000WAH|U9|PTN78000WAH|PTN78000H|1|PTN78000WAH|296-20506-ND|
54|Voltage reference, 5V|REF02CSZ|U7|REF02CSZ|SOIC-8_3.9x4.9mm_Pitch1.27mm|1|REF02CSZ|REF02CSZ-ND|
55|Two pin crystal|Crystal|Y2|10MHz|Crystal_HC49-4H_Vertical|1|9B-10.000MEEJ-B|887-1235-ND|
56|Two pin crystal|Crystal|Y1|8MHz|Crystal_HC49-4H_Vertical|1|9B-8.000MEEJ-B|887-1233-ND|
57|Microcontroller, dsPIC30, SMT|dsPIC30F4013|dsPIC1|dsPIC30F4013|TQFP-44_10x10mm_Pitch0.8mm|1|DSPIC30F4013-30I/PT|DSPIC30F401330IPT-ND|





Component Groups:|57
Component Count:|212
Fitted Components:|212
Number of PCBs:|1
Total components:|212
Schematic Version:|REV D
Schematic Date:|2018-01-04
BoM Date:|Wed 10 Jan 2018 09:00:42 PM CST
Schematic Source:|/home/vic/svn_root/BBB_HVAC/SCHEMATICS/VIOBOARD/VIOBOARD.sch
KiCad Version:|Eeschema 4.0.7-e2-6376~58~ubuntu16.04.1

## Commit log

2018-09-03 Initial import
2018-11-25 Schematics as sent to PCB manufacture.
2018-11-25 Libraries modified as part of the BBB cape developement.
2019-06-23 Added a selction of custom footprints
2019-06-23 Added data sheets for specific components.
2019-06-23 Added more ignores.
2019-06-23 Added files to ignore.
2019-06-23 Shared schematics update.
2019-06-23 Changed to high-side switching of power supply to boards. Changed footprints to SOIC. Misc other changes.
2019-06-24 Added footprints for a 1206-WIDE shunt and a KSC3 surface mount tactile button.
2019-06-24 Cleaned up the crow-bar circuit schematic.
2019-06-24 Added datasheet for tactile switch.
2019-06-24 Cleaned up schematic.
2019-07-07 Added data sheet for spring terminals.
2019-07-07 Added -rescue.dcm to .gitignore
2019-07-07 Added 10 position spring terminal to footprint library from the G4 IO project. Removed outline. Added 1x6 2.54 mm pin header. Modified by removing outline.
2019-07-07 Added 1206 WIDE footprint with measurement pads. Added TO-277 diode footprint. Added MSOP-10 footprint.
2019-07-07 Cleaned up power protection sheet.
2019-07-07 Schematic cleanup and refinement.
2019-07-08 Copied the previous fabrication files.
2019-07-08 Part of move of old fab files. Can't seem to get git right.
2019-07-11 Submited to board fab.
2019-08-06 Rev 2 problem fixes.
2019-09-24 Schematics cleanup. Gerbers for the latest manufacturing release.
